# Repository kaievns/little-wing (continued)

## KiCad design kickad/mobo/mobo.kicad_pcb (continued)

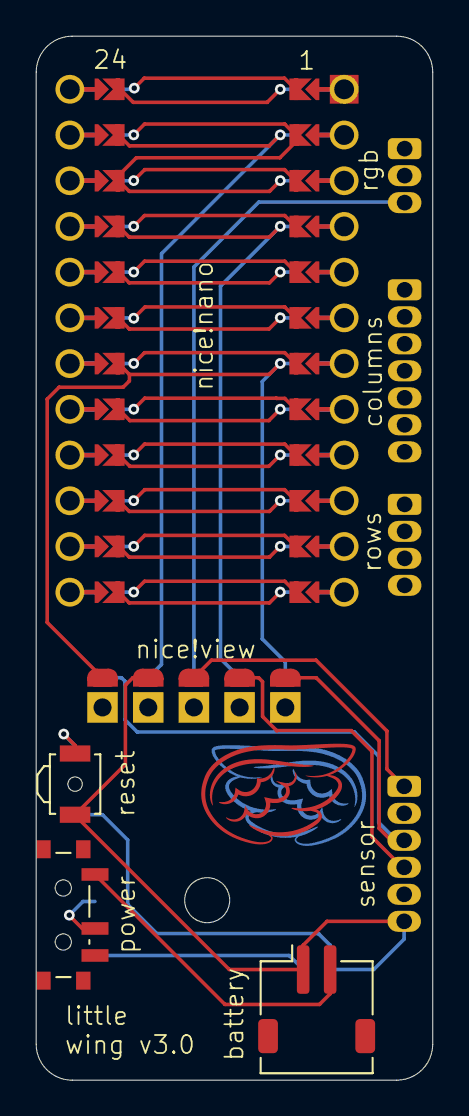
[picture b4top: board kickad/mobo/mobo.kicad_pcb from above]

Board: 4 copper layers, 22.0 x 58.0 mm, 9 parts (0 on the bottom side), 22 nets.

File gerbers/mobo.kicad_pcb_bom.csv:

Designator,Quantity,Value,Footprint,Package,MPN,DNP,Mount_Type,Description
J1,1,nice!view,OLED-128x32-double-sided,,,,tht,"Generic connector, single row, 01x05, script generated"
J12,1,columns,Wuerth_WR-WTB_64800711622_1x07_P1.50mm_Vertical,,,,tht,"Generic connector, single row, 01x07, script generated"
J2,1,Battery,JST_ZH_S2B-ZR-SM4A-TF_1x02-1MP_P1.50mm_Horizontal,,,,smt,"Generic connector, single row, 01x02, script generated (kicad-library-utils/schlib/autogen/connector/)"
J4,1,sensor,Wuerth_WR-WTB_64800611622_1x06_P1.50mm_Vertical,,,,tht,"Generic connector, single row, 01x06, script generated"
J8,1,rgb,Wuerth_WR-WTB_64800311622_1x03_P1.50mm_Vertical,,,,tht,"Generic connector, single row, 01x03, script generated"
J9,1,rows,Wuerth_WR-WTB_64800411622_1x04_P1.50mm_Vertical,,,,tht,"Generic connector, single row, 01x04, script generated"
SW1,1,Power,SW_SPDT_PCM12,,,,smt,"Push button switch, generic, two pins"
SW2,1,Reset,SW_SPST_B3U-3000P-B,,,,smt,"Push button switch, generic, two pins"
U1,1,nice!nano v2,ProMicro_independent_flipped,,,,tht,

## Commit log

2024-08-05 Initial setup
2024-08-07 Initial PCB layout
2024-08-07 Flipping the components in place
2024-08-08 Remaking the PCB for better alignment
2024-08-09 Stashing the work before extending the cutouts
2024-08-10 Making a column work
2024-08-10 Sorting out the main reversible pads
2024-08-11 Connecting the reversible pads together
2024-08-11 Saving the main lanes progress
2024-08-13 Linking all the main columns together
2024-08-13 Initial alignment of the sensor block
2024-08-13 Wiring togother the sensor board
2024-08-14 Rounding out the main columns cutouts
2024-08-14 Refactoring the main junction a bit
2024-08-15 Initial MCU wiring
2024-08-16 Wiring up the MCU block
2024-08-17 Finalizing the wiring
2024-08-17 Repairing the cutouts and adding the flex markings
2024-08-17 Clearing out all the wiring
2024-08-18 Rewiring one column in the 4 stack configuration
2024-08-18 Wiring up all the main column pads
2024-08-18 Wiring up the main columns
2024-08-18 The first pass wiring together the columns
2024-08-18 Adding the readme
2024-08-18 Completing the columns wiring
2024-08-18 Cleaning up the columns wiring
2024-08-18 Cleaning up the main columns exit wiring
2024-08-18 Attaching the columns to MCU
2024-08-20 Wiring together the thumbs cluster
2024-08-20 Re-aligning a few things to make the ribbons more flexible and avoid cross talk
2024-08-20 Spit and polish
2024-08-25 Adding the left/right hand split
2024-08-25 Syncing the schematics and pcb
2024-08-25 Setting up the new grid outline
2024-08-26 Creating the reusable key pad
2024-08-26 Making a stack of panels
2024-08-27 Lining up some extra sockets for wiring
2024-08-27 Lining up the cable wiring points
2024-08-28 Lining up the main board components
2024-08-28 Wiring together the mobos
2024-08-29 Sorting out silk screens
2024-08-29 Final touches for the mobos
2024-08-29 Rewiring the trackball sensor PCB
2024-08-29 Some more clean up
2024-09-17 Swapping out some components
2024-09-17 Reconnecting all the components on PCB again
2024-09-17 Rearranging things a bit
2024-09-17 Realigning the panel elements
2024-09-17 Adding the mouse bites
2024-09-18 Adding the breakaway arks
2024-09-18 Stitching all the sub-pcbs into a panel
2024-09-18 Adding manufacturing panels
2024-10-05 Moving all the kicads into its own folder
2024-10-05 Dumping the initial zmk config
2024-10-05 Adding a dummy keymap
2024-10-06 Making the initial setup compilable
2024-10-06 Adding some basic RGB support
2024-10-07 Making the displays sort of work
2024-10-11 Stashing the work
2024-10-14 Stashig the work
2024-10-17 Making the sensor somewhat working
2024-10-17 Removing submodule
2024-10-23 Making different drivers compile again
2024-10-26 Reworking the about rotation settings
2024-10-26 Making the mouse layers work
2024-10-27 Trackball settings tweaks
2024-10-27 Re-enabling the uderglow
2024-10-27 Stashig some nice!view work
2024-10-27 Backporting my old keymaps stuff
2024-10-28 Moving the trackball def into the right side
2024-10-29 Making the input-split work
2024-10-29 Small tweaks and such
2024-10-29 Making the mouse and scroll layers transparrent to reduce the change lag
2024-10-30 Trying to swap sides
2024-11-02 Stashing tweaks
2024-11-02 A few more tweaks
2024-11-03 Dropping the CPI a little bit
2025-01-04 Reworking the schematics for a smaller power stepdown unit
2025-01-04 Updating the pmw3610 driver
2025-01-04 Stashing some of the patches
2025-01-04 Making the firmware compile again
2025-01-05 Intergating the nice-view displays back
2025-01-05 Patching the display select pin
2025-01-11 Throwing in the new PCB outline for the optical sensor
2025-01-12 Stashing work
2025-01-18 Splitting the KiCAD project into thre independent PCBs
2025-01-18 Reworking the sensor PCB
2025-03-28 Resetting the mobo stack to 4 layers mirrorable
2025-03-29 Reworking the mobo into a reversible panel
2025-03-29 Reworking the keypad PCB
2025-03-29 Releasing all the gerbers
2025-05-03 Stashing pcb changes
2025-05-03 Patching some of the wiring
2025-05-04 Upgrading the optical driver to support multi-device SPIs
2025-05-04 Stashing right side work
2025-05-04 Making the trackball sort of work
2025-05-07 Random patches tweaks improvements
2025-05-14 Moving the main half to the right side to simplify trackball handling
2025-05-14 Patching the scrolling logic
2025-05-21 More patches
2025-09-24 Stashing driver changes
2025-09-24 Dumping everything i need into the combined schematic
2025-09-27 Cleaning up the schematics
2025-09-27 Resetting the PCB
2025-09-27 Replacing the through holes with JST-SH connectors
2025-10-07 Adding connectors 3d files
2025-10-11 Assigning all the perifery pins
2025-10-11 Groupping around the PCB components
2025-10-12 Loosely optimising the groups components placement
2025-10-12 Groupping the groups into a workable arrangement
2025-10-12 Sub-compacting the components to their target dimensions
2025-10-12 Partially wiring the bottom half
2025-11-07 Importing reference schematics for nrf52840 and npm1100 chips and renaming the project
2025-11-07 Re-shuffling the schematics across sub-sheets
2025-11-07 Copying over the reference PCB stacks
2025-11-08 Tidying up the mess a little bit
2025-11-09 Re-importing some key components
2025-11-09 Adding the antennae
2025-11-09 Removing the NFC1/2 connectors
2025-11-09 Cleaning up the PSU schematics
2025-11-10 Cleaning up the schematics a bit more
2025-11-11 Updating schematics/pcb to match the labels
2025-11-12 Cleaning up some space on the PCB
2025-11-12 Reseting all the extra components sizes
2025-11-12 Dissolving and re-packaging the PSU block
2025-11-12 Unshielding the main block
2025-11-12 Swapping the crystals for smaller ones
2025-11-13 Dialing in the physical package
2025-11-13 Putting all the components in their rough places
2025-11-14 Backporting footprints from the PCB back to schematic
2025-11-14 Fixes and space optimisations
2025-11-15 Loosely attaching pins to prefiery
2025-11-15 More routing
2025-11-15 Connecting most of the other components
2025-11-16 Connecting remaining power lines
2025-11-16 Adding the J-tag connector for the programmer
2025-11-16 Adding the solid ground fill
2025-11-17 Adding the Plan B pins
2025-11-17 Re-organising the schematics sheets a bit
2025-11-18 Reworking the RGB power section
2025-11-19 Moving the RGB feed capacitor
2025-11-23 Removing the RGB level shifter
